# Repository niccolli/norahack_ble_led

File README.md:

# 野良HACK BLE〜LEDブリッジ基板

[技術書典7 け27D](https://techbookfest.org/event/tbf07/circle/5663970140618752) にて頒布するBLE〜LEDブリッジ基板の製造データです。

## 各種制御ソフトウェア

- [M5Stack用](https://github.com/da-eee/CNoraBLE)
- [FirebaseとEnebular](https://github.com/muramasa2764/ESP32Firebase-BLE)
- [Web Bluetoothデモ](https://pokiiio.github.io/Jones/)

## 製造データ

### 回路図

output/Schematic.pdf をお読みください。

### ガーバー

output/Gerberフォルダ内を参照ください。

参考までに、[FusionPCB](https://www.seeedstudio.com/fusion.html)に発注した際の設定を記載します。

- PCB Dimension - 32mm*32mm 
- Impedance Control - No 
- Surface Finish - Hasl(Lead Free) 
- Min Solder Mask Dam - 0.4mm↑ 
- Copper Weight - 1oz. 
- Half-cut / Castellated Holes - No 
- Min Hole Size - 0.3mm 
- PCB Color - Green 
- Material - FR4 TG130 
- Layer - 2 
- PCB Qty. - 50 
- Blind Vias - No 
- PCB Thickness - 1.6mm 
- Min Tracking / Spacing - 6/6mil 
- Panelized PCBs - 1 
- Expedited Option - No 

### 部品表

[こちら](https://docs.google.com/spreadsheets/d/1IFBm3dJIjSWrcvgrVqms4TnD1tUxHpUHN8ivpyQduAM/edit?usp=sharing)を参照ください。

## 基板取り扱いの諸注意

### 電池・電源について

- 乾電池は4本以上直列に接続しないでください。BLEマイコンに供給するLDOの最大定格が6Vのため、4本以上接続すると電源が故障します。
- 乾電池が2本ではLEDが点灯しません。ただし、LEDを接続せずBLEマイコンのみ使用する場合は2本でも問題ありません。

### ファームウェアの書き込みについて

J2またはJ3にピンをはんだづけすることで、BLEモジュールのファームウェアを書き換えることができます。

J-LINK EDUやLiteを使用する場合はJ3、STMicroのNucleoボードのST-LINKを書き換えて使う場合はJ2が便利です。どちらも結線は同じですので、用途に合わせてお選びください。

### シリアル通信について

基板裏面にシリアル通信用のパッドを引き伸ばしています。もちろんGPIOとしても使えますので、是非ご活用ください。

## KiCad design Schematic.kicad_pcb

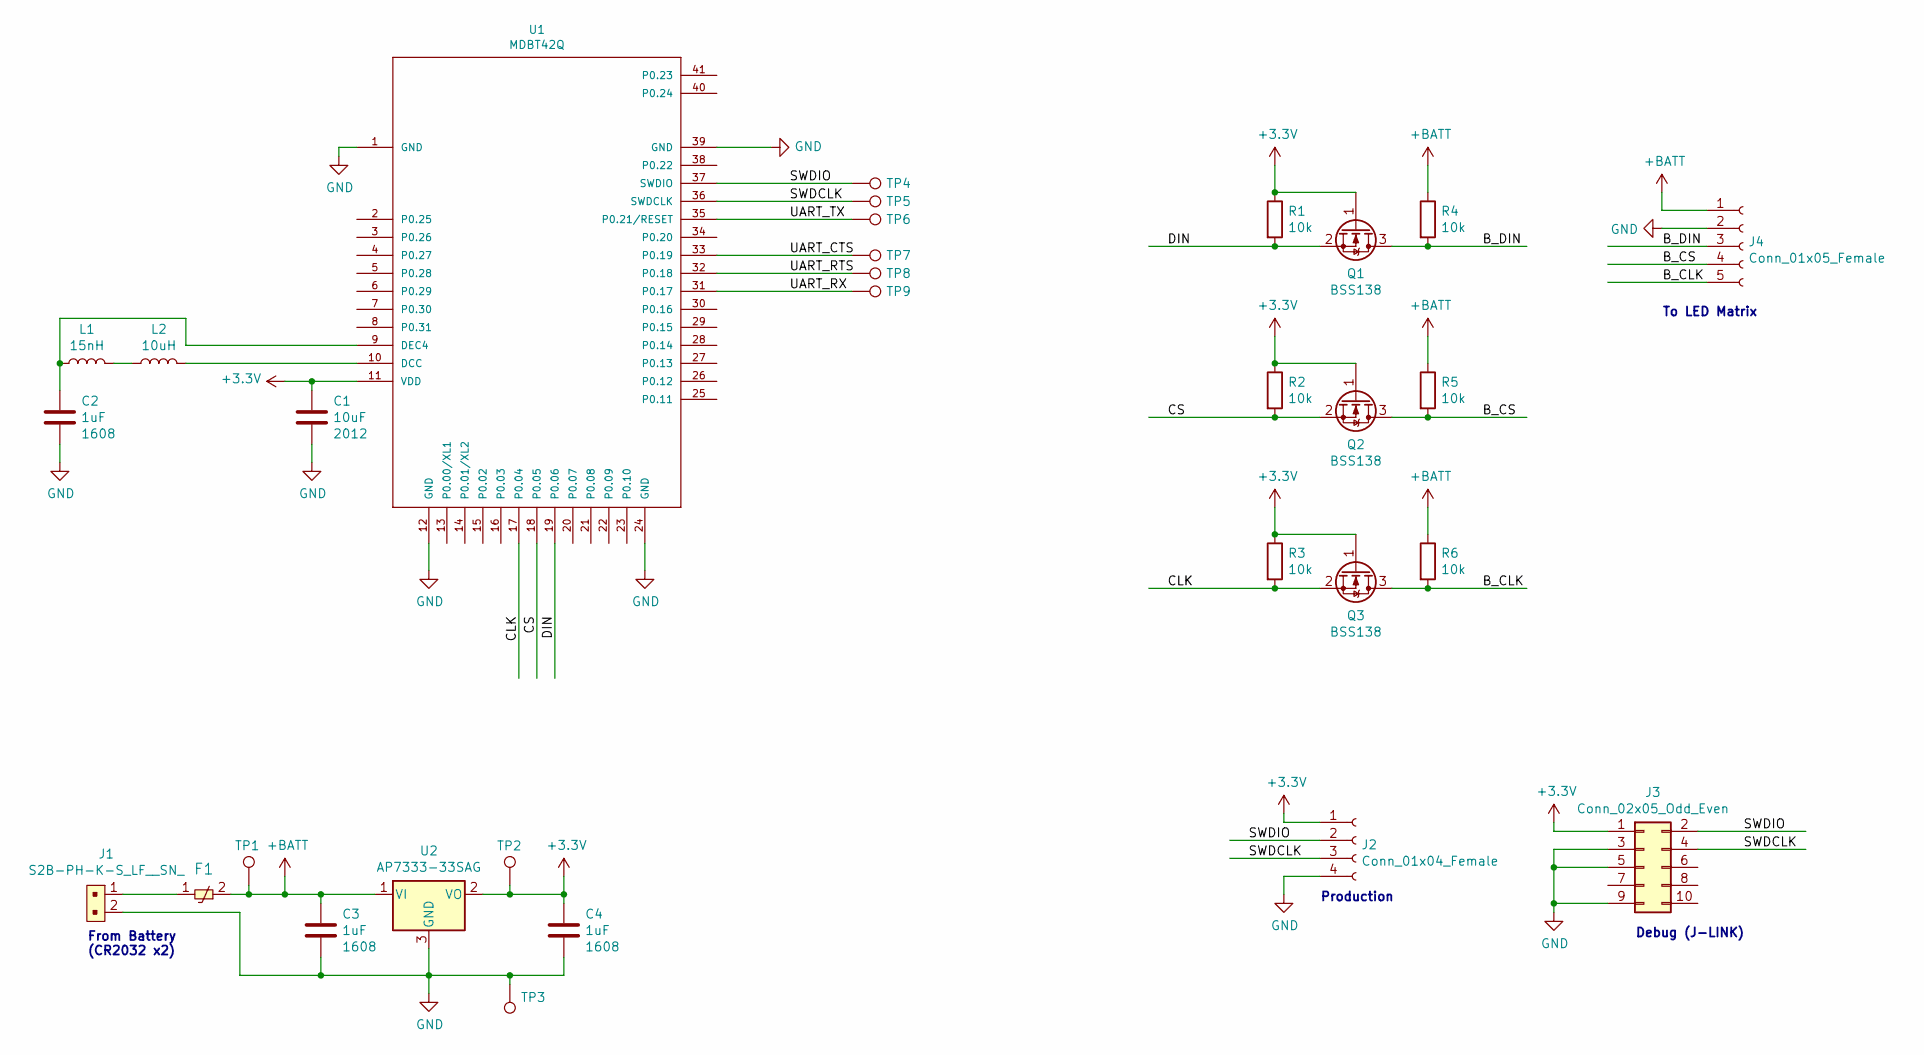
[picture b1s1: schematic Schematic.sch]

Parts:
C1: 10uF; C_0805_2012Metric_Pad1.15x1.40mm_HandSolder
C2, C3, C4: 1uF; C_0603_1608Metric_Pad1.05x0.95mm_HandSolder
F1: FEMTOSMDC010F-02; Fuse_0603_1608Metric_Pad1.05x0.95mm_HandSolder; MPN AS32 2R025
J1: S2B-PH-K-S_LF__SN_; PinHeader_1x2_P2mm_Drill1mm_RA; MPN S2B-PH-K-S(LF)(SN); Digi-Key_PN 455-1719-ND
J2: Conn_01x04_Female; PinHeader_1x04_P2.54mm_Vertical
J3: Conn_02x05_Odd_Even; PinHeader_2x05_P1.27mm_Vertical_SMD
J4: Conn_01x05_Female; PinHeader_1x05_P2.54mm_Horizontal
L1: 15nH; L_0603_1608Metric_Pad1.05x0.95mm_HandSolder; PartName HK160815NJ-T
L2: 10uH; L_0805_2012Metric_Pad1.15x1.40mm_HandSolder; PartName LBR2012T100K
Q1, Q2, Q3: BSS138; SOT-23
R1, R2, R3, R4, R5, R6: 10k; R_0603_1608Metric_Pad1.05x0.95mm_HandSolder
TP1, TP2, TP3, TP4, TP5, TP6, TP7, TP8, TP9: TestPoint; TestPoint_Pad_D1.5mm
U1: MDBT42Q
U2: AP7333-33SAG; SOT-23

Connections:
+3V3: C1.1, C4.1, J2.1, J3.1, Q1.1 (G), Q2.1 (G), Q3.1 (G), R1.1, R2.1, R3.1, TP2.1, U1.11 (VDD), U2.2 (VO)
+BATT: C3.1, F1.2, J4.1, R4.1, R5.1, R6.1, TP1.1, U2.1 (VI)
/B_CLK: J4.5, Q3.3 (D), R6.2
/B_CS: J4.4, Q2.3 (D), R5.2
/B_DIN: J4.3, Q1.3 (D), R4.2
/CLK: Q3.2 (S), R3.2, U1.17 (P0.04)
/CS: Q2.2 (S), R2.2, U1.18 (P0.05)
/DIN: Q1.2 (S), R1.2, U1.19 (P0.06)
/SWDCLK: J2.3, J3.4, TP5.1, U1.36 (SWDCLK)
/SWDIO: J2.2, J3.2, TP4.1, U1.37 (SWDIO)
/UART_CTS: TP7.1, U1.33 (P0.19)
/UART_RTS: TP8.1, U1.32 (P0.18)
/UART_RX: TP9.1, U1.31 (P0.17)
/UART_TX: TP6.1, U1.35 (P0.21/RESET)
GND: C1.2, C2.2, C3.2, C4.2, J1.2, J2.4, J3.3, J3.5, J3.9, J4.2, TP3.1, U1.1 (GND), U1.12 (GND), U1.24 (GND), U1.39 (GND), U2.3 (GND)
unnamed: C2.1, L1.1, U1.9 (DEC4)
unnamed: F1.1, J1.1
unnamed: L1.2, L2.1
unnamed: L2.2, U1.10 (DCC)

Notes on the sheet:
To LED Matrix
Debug (J-LINK)
Production
From Battery (CR2032 x2)

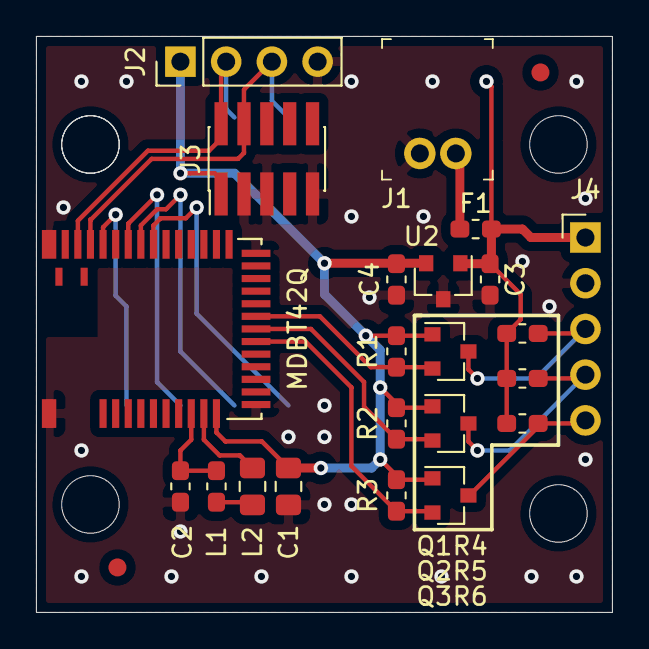
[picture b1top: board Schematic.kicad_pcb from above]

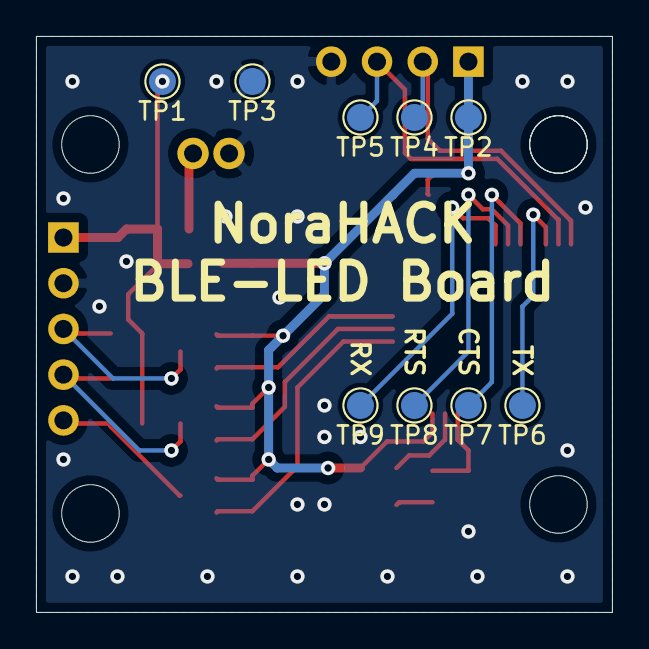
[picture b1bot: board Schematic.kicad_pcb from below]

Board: 2 copper layers, 32.0 x 32.0 mm, 31 parts (9 on the bottom side), 19 nets.

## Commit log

2019-08-25 Added schematic PDF
2019-09-21 TP等を追加
2019-09-21 回路図とガーバーを出力
2019-09-21 ガーバーと回路図の区別がわかりにくかったので対処
2019-09-21 .gitignoreを設定し、不要なファイルを削除。
2019-09-21 READMEの初稿を投稿
2019-09-21 制御ソフトのリンクを追加
